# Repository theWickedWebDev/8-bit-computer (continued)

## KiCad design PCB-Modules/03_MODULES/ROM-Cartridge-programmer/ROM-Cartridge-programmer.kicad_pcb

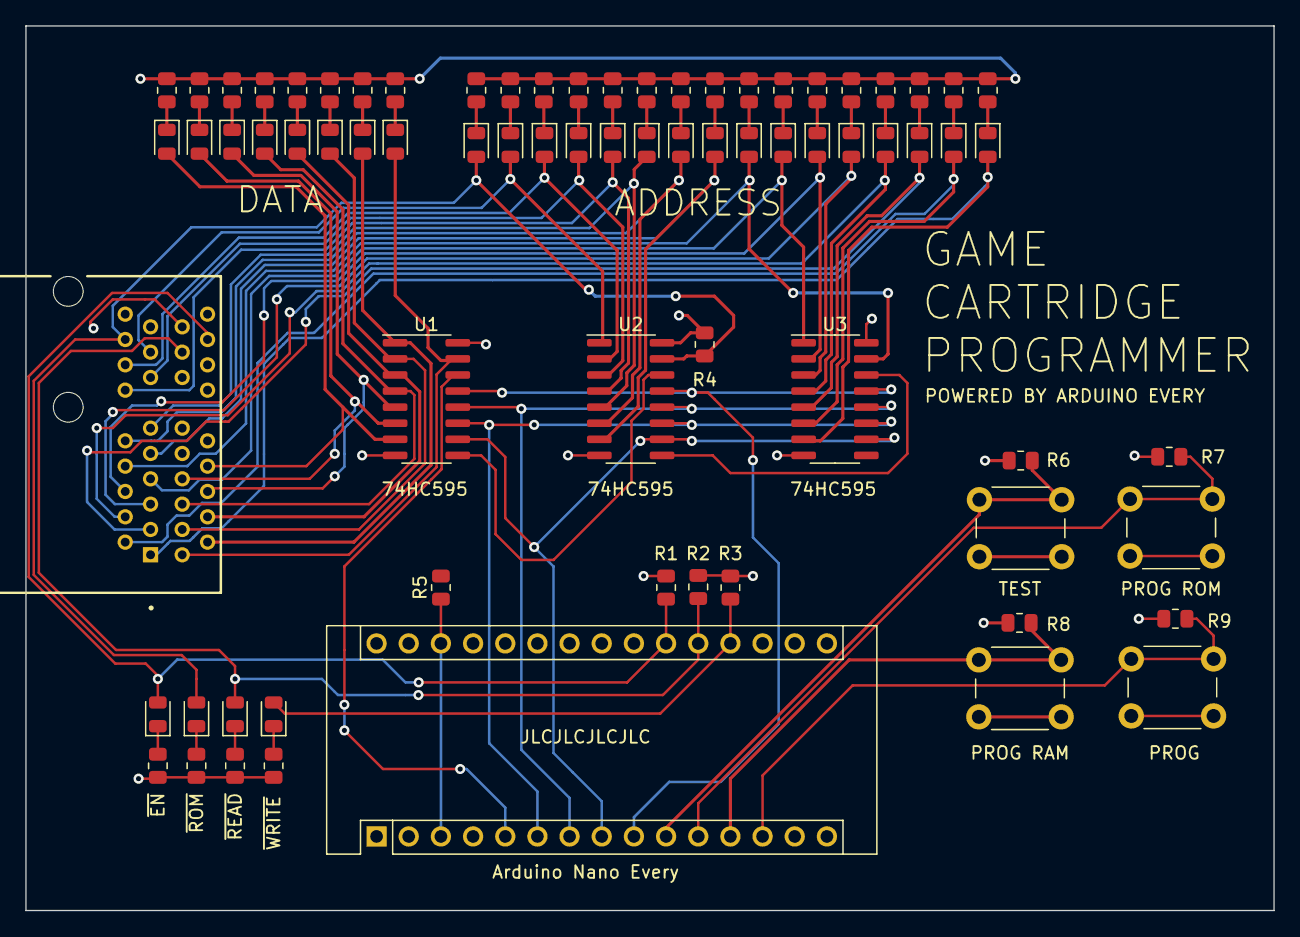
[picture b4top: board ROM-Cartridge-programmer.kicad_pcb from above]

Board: 4 copper layers, 98.6 x 69.8 mm, 74 parts (0 on the bottom side), 69 nets.

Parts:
A1: Arduino_Nano_Every; Arduino_Nano
D1, D2, D3, D4, D5, D6, D7, D8, D9, D10, D11, D12, D13, D14, D15, D16, D17, D18, D19, D20, D21, D22, D23, D24, D25, D26, D27, D28: LED; LED_0805_2012Metric
J1: PCIE-036-02-X-D-RA; SAMTEC_PCIE-036-02-X-D-RA
R1, R2, R3, R4, R5, R6, R7, R8, R9, R10, R11, R12, R13, R14, R15, R16, R17, R18, R19, R20, R21, R22, R23, R24, R25, R26, R27, R28, R29, R30, R31, R32, R33, R34, R35, R36, R37: R_Small_US; R_0805_2012Metric
SW1, SW2, SW3, SW4: SW_Push; SW_PUSH_6mm
U1, U2, U3: 74HC595; SOIC-16_3.9x9.9mm_P1.27mm

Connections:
/A0: D16.2 (A), J1.A01, U3.7 (QH)
/A1: D15.2 (A), J1.A02, U3.6 (QG)
/A2: D14.2 (A), J1.A03, U3.5 (QF)
/A3: D13.2 (A), J1.A04, U3.4 (QE)
/A4: D12.2 (A), J1.A05, U3.3 (QD)
/A5: D11.2 (A), J1.A06, U3.2 (QC)
/A6: D10.2 (A), J1.A07, U3.1 (QB)
/A7: D9.2 (A), J1.A08, U3.15 (QA)
/A8: D8.2 (A), J1.A09, U2.7 (QH)
/A9: D7.2 (A), J1.A10, U2.6 (QG)
/A10: D6.2 (A), J1.A11, U2.5 (QF)
/A11: D5.2 (A), J1.A12, U2.4 (QE)
/A12: D4.2 (A), J1.A13, U2.3 (QD)
/A13: D3.2 (A), J1.A14, U2.2 (QC)
/A14: D2.2 (A), J1.A15, U2.1 (QB)
/A15: D1.2 (A), D28.2 (A), J1.A16, R4.1, U2.15 (QA)
/CLOCK: A1.6 (D3), U1.11 (SRCLK), U2.11 (SRCLK), U3.11 (SRCLK)
/D0: D24.2 (A), J1.B01, U1.15 (QA)
/D1: D23.2 (A), J1.B02, U1.1 (QB)
/D2: D22.2 (A), J1.B03, U1.2 (QC)
/D3: D21.2 (A), J1.B04, U1.3 (QD)
/D4: D20.2 (A), J1.B05, U1.4 (QE)
/D5: D19.2 (A), J1.B06, U1.5 (QF)
/D6: D18.2 (A), J1.B07, U1.6 (QG)
/D7: D17.2 (A), J1.B08, U1.7 (QH)
/DATA: A1.5 (D2), U1.14 (SER)
/LATCH: A1.7 (D4), U1.12 (RCLK), U2.12 (RCLK), U3.12 (RCLK)
/PRAM: A1.12 (D9), R8.2, SW3.1
/PROG: A1.13 (D10), R9.2, SW4.1
/PROM: A1.11 (D8), R7.2, SW2.1
/TEST: A1.10 (D7), R6.2, SW1.1
/~EN: A1.21 (A2), D27.2 (A), J1.B16, R1.1
/~READ: A1.20 (A1), D26.2 (A), J1.B15, R2.1
/~RESET: A1.8 (D5), U1.10 (~SRCLR), U2.10 (~SRCLR), U3.10 (~SRCLR)
/~SR_OE: A1.9 (D6), U1.13 (~OE), U2.13 (~OE), U3.13 (~OE)
/~WRITE: A1.19 (A0), D25.2 (A), R3.1
GND: A1.4 (GND), A1.29 (GND), J1.B17, R1.2, R6.1, R7.1, R8.1, R9.1, R10.1, R11.1, R12.1, R13.1, R14.1, R15.1, R16.1, R17.1, R18.1, R19.1, R20.1, R21.1, R22.1, R23.1, R24.1, R25.1, R26.1, R27.1, R28.1, R29.1, R30.1, R31.1, R32.1, R33.1, R34.1, R35.1, R36.1, R37.1, U1.8 (GND), U2.8 (GND), U3.8 (GND)
unnamed: A1.3 (~RESET), A1.28 (~RESET), R5.1
unnamed: D1.1 (K), R10.2
unnamed: D2.1 (K), R11.2
unnamed: D3.1 (K), R12.2
unnamed: D4.1 (K), R13.2
unnamed: D5.1 (K), R14.2
unnamed: D6.1 (K), R15.2
unnamed: D7.1 (K), R16.2
unnamed: D8.1 (K), R17.2
unnamed: D9.1 (K), R18.2
unnamed: D10.1 (K), R19.2
unnamed: D11.1 (K), R20.2
unnamed: D12.1 (K), R21.2
unnamed: D13.1 (K), R22.2
unnamed: D14.1 (K), R23.2
unnamed: D15.1 (K), R24.2
unnamed: D16.1 (K), R25.2
unnamed: D17.1 (K), R26.2
unnamed: D18.1 (K), R27.2
unnamed: D19.1 (K), R28.2
unnamed: D20.1 (K), R29.2
unnamed: D21.1 (K), R30.2
unnamed: D22.1 (K), R31.2
unnamed: D23.1 (K), R32.2
unnamed: D24.1 (K), R33.2
unnamed: D25.1 (K), R34.2
unnamed: D26.1 (K), R35.2
unnamed: D27.1 (K), R36.2
unnamed: D28.1 (K), R37.2
unnamed: U2.9 (QH'), U3.14 (SER)
unnamed: U1.9 (QH'), U2.14 (SER)
VCC: A1.27 (+5V), J1.B18, R2.2, R3.2, R4.2, R5.2, SW1.2, SW2.2, SW3.2, SW4.2, U1.16 (VCC), U2.16 (VCC), U3.16 (VCC)

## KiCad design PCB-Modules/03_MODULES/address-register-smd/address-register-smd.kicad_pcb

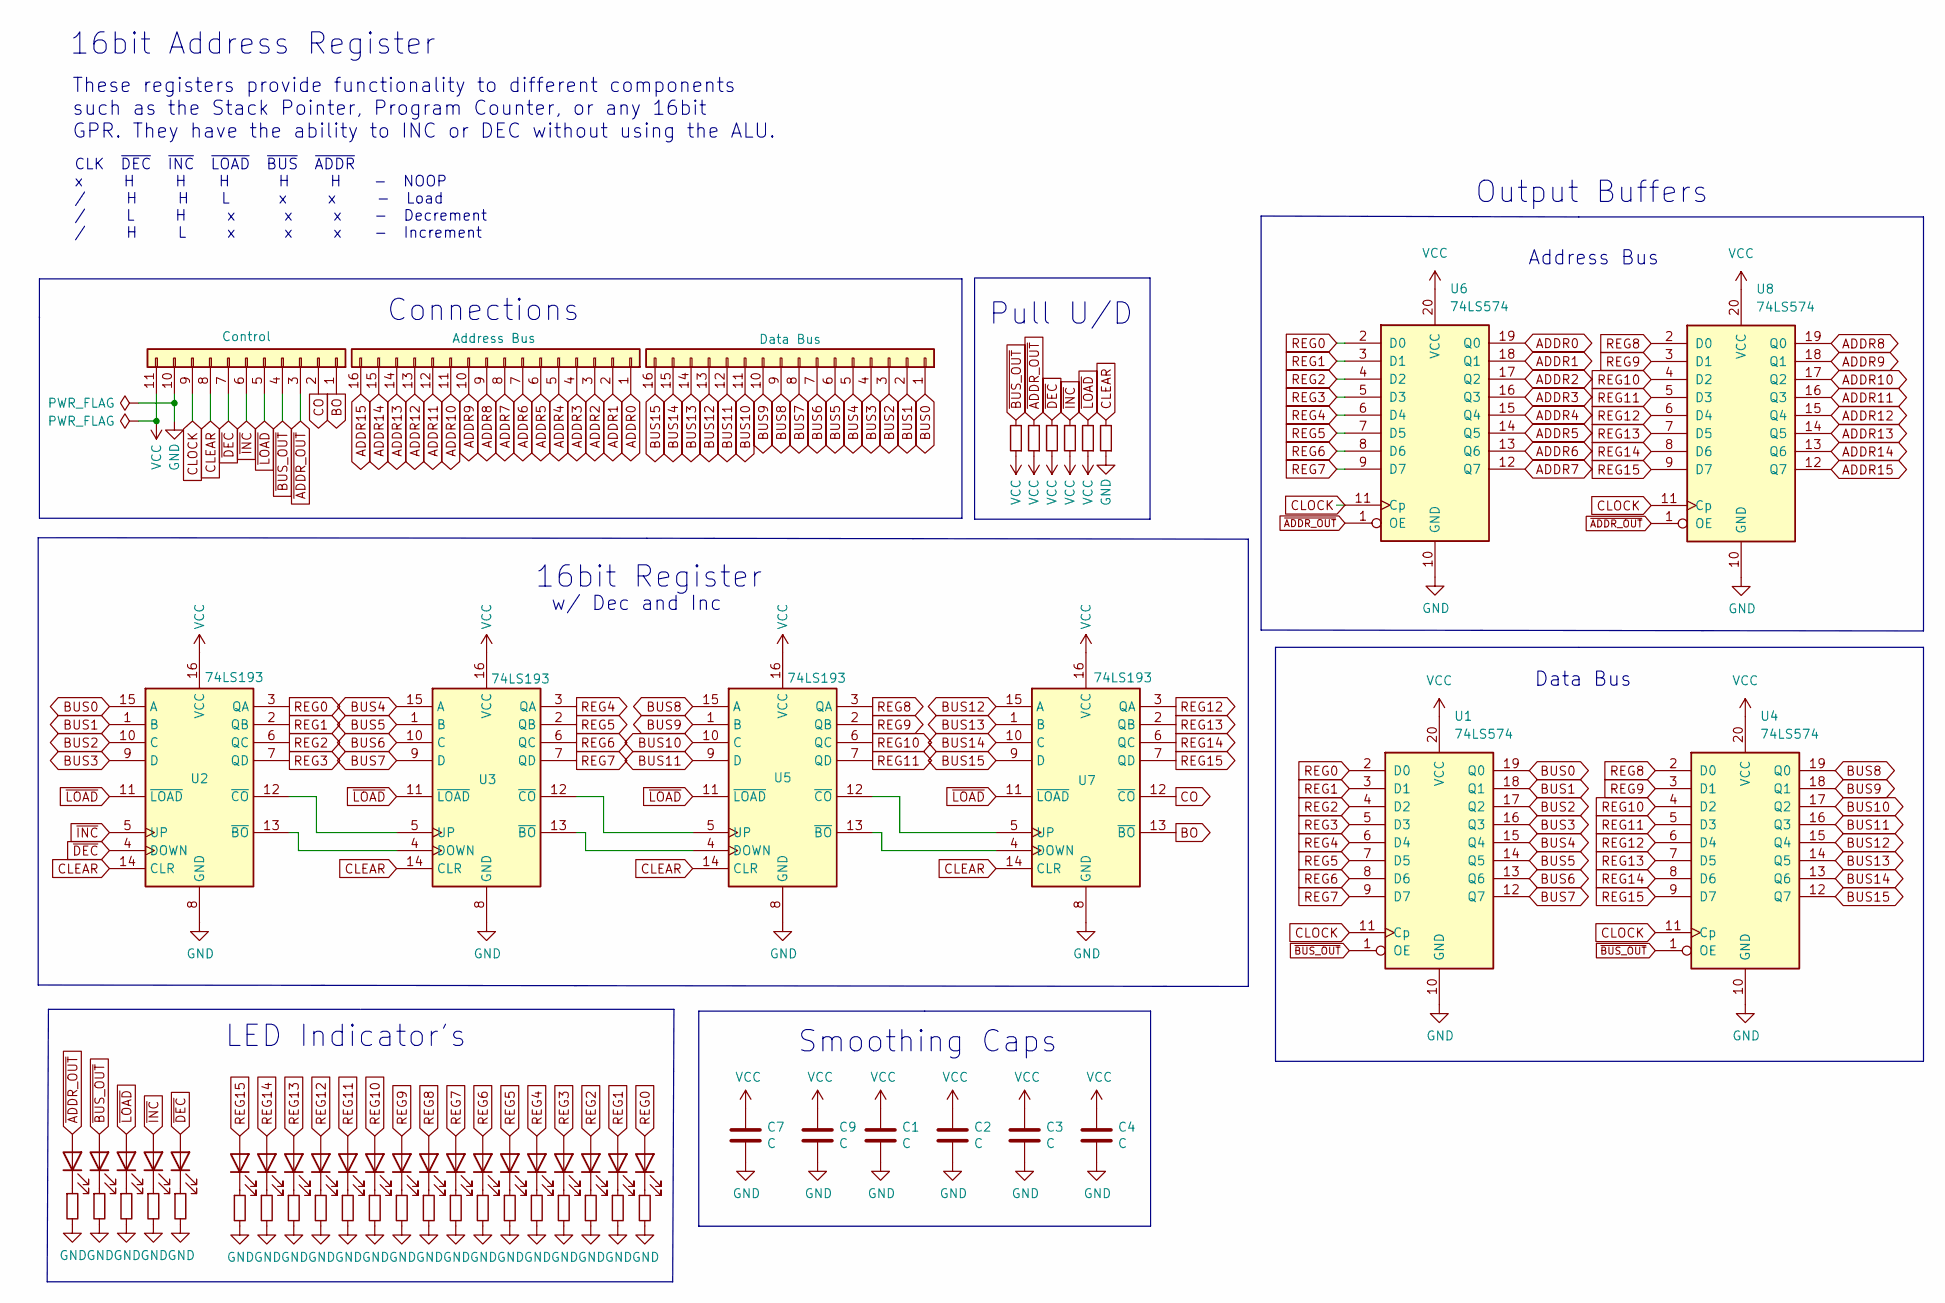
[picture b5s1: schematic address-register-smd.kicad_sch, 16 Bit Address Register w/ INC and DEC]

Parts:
C1, C2, C3, C4, C7, C9: C; C_0805_2012Metric
D1, D2, D3, D4, D5, D6, D7, D8, D9, D10, D11, D12, D13, D14, D15, D16, D18, D19, D20, D21, D22: LED; LED_1206_3216Metric
J2, J3: Conn_01x16; PinHeader_1x16_P2.54mm_Vertical
J4: Conn_01x11; PinHeader_1x11_P2.54mm_Vertical
R1, R2, R3, R4, R5, R6, R7, R8, R9, R10, R11, R12, R13, R14, R15, R16, R17, R18, R19, R20, R21, R22, R23, R24, R25, R27, R28: R_Small; R_0805_2012Metric
U1, U4, U6, U8: 74LS574; SO-20_5.3x12.6mm_P1.27mm
U2, U3, U5, U7: 74LS193; SO-16_5.3x10.2mm_P1.27mm

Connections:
ADDR0: J3.1, U6.19 (Q0)
ADDR1: J3.2, U6.18 (Q1)
ADDR2: J3.3, U6.17 (Q2)
ADDR3: J3.4, U6.16 (Q3)
ADDR4: J3.5, U6.15 (Q4)
ADDR5: J3.6, U6.14 (Q5)
ADDR6: J3.7, U6.13 (Q6)
ADDR7: J3.8, U6.12 (Q7)
ADDR8: J3.9, U8.19 (Q0)
ADDR9: J3.10, U8.18 (Q1)
ADDR10: J3.11, U8.17 (Q2)
ADDR11: J3.12, U8.16 (Q3)
ADDR12: J3.13, U8.15 (Q4)
ADDR13: J3.14, U8.14 (Q5)
ADDR14: J3.15, U8.13 (Q6)
ADDR15: J3.16, U8.12 (Q7)
BO: J4.1, U7.13 (~BO)
BUS0: J2.1, U1.19 (Q0), U2.15 (A)
BUS1: J2.2, U1.18 (Q1), U2.1 (B)
BUS2: J2.3, U1.17 (Q2), U2.10 (C)
BUS3: J2.4, U1.16 (Q3), U2.9 (D)
BUS4: J2.5, U1.15 (Q4), U3.15 (A)
BUS5: J2.6, U1.14 (Q5), U3.1 (B)
BUS6: J2.7, U1.13 (Q6), U3.10 (C)
BUS7: J2.8, U1.12 (Q7), U3.9 (D)
BUS8: J2.9, U4.19 (Q0), U5.15 (A)
BUS9: J2.10, U4.18 (Q1), U5.1 (B)
BUS10: J2.11, U4.17 (Q2), U5.10 (C)
BUS11: J2.12, U4.16 (Q3), U5.9 (D)
BUS12: J2.13, U4.15 (Q4), U7.15 (A)
BUS13: J2.14, U4.14 (Q5), U7.1 (B)
BUS14: J2.15, U4.13 (Q6), U7.10 (C)
BUS15: J2.16, U4.12 (Q7), U7.9 (D)
CLEAR: J4.8, R18.2, U2.14 (CLR), U3.14 (CLR), U5.14 (CLR), U7.14 (CLR)
CLOCK: J4.9, U1.11 (Cp), U4.11 (Cp), U6.11 (Cp), U8.11 (Cp)
CO: J4.2, U7.12 (~CO)
GND: C1.2, C2.2, C3.2, C4.2, C7.2, C9.2, J4.10, R2.2, R3.2, R4.2, R5.2, R6.2, R7.2, R8.2, R9.2, R10.2, R11.2, R12.2, R13.2, R14.2, R15.2, R16.2, R17.2, R18.1, R19.2, R20.2, R21.2, R22.2, R23.2, U1.10 (GND), U2.8 (GND), U3.8 (GND), U4.10 (GND), U5.8 (GND), U6.10 (GND), U7.8 (GND), U8.10 (GND)
unnamed: D1.1 (K), R2.1
unnamed: D2.1 (K), R3.1
unnamed: D3.1 (K), R4.1
unnamed: D4.1 (K), R5.1
unnamed: D5.1 (K), R6.1
unnamed: D6.1 (K), R7.1
unnamed: D7.1 (K), R8.1
unnamed: D8.1 (K), R9.1
unnamed: D9.1 (K), R10.1
unnamed: D10.1 (K), R11.1
unnamed: D11.1 (K), R12.1
unnamed: D12.1 (K), R13.1
unnamed: D13.1 (K), R14.1
unnamed: D14.1 (K), R15.1
unnamed: D15.1 (K), R16.1
unnamed: D16.1 (K), R19.1
unnamed: D18.1 (K), R20.1
unnamed: D19.1 (K), R21.1
unnamed: D20.1 (K), R22.1
unnamed: D21.1 (K), R23.1
unnamed: D22.1 (K), R17.1
unnamed: U2.12 (~CO), U3.5 (UP)
unnamed: U2.13 (~BO), U3.4 (DOWN)
unnamed: U3.12 (~CO), U5.5 (UP)
unnamed: U3.13 (~BO), U5.4 (DOWN)
unnamed: U5.12 (~CO), U7.5 (UP)
unnamed: U5.13 (~BO), U7.4 (DOWN)
REG0: D16.2 (A), U1.2 (D0), U2.3 (QA), U6.2 (D0)
REG1: D15.2 (A), U1.3 (D1), U2.2 (QB), U6.3 (D1)
REG2: D14.2 (A), U1.4 (D2), U2.6 (QC), U6.4 (D2)
REG3: D13.2 (A), U1.5 (D3), U2.7 (QD), U6.5 (D3)
REG4: D12.2 (A), U1.6 (D4), U3.3 (QA), U6.6 (D4)
REG5: D11.2 (A), U1.7 (D5), U3.2 (QB), U6.7 (D5)
REG6: D10.2 (A), U1.8 (D6), U3.6 (QC), U6.8 (D6)
REG7: D9.2 (A), U1.9 (D7), U3.7 (QD), U6.9 (D7)
REG8: D8.2 (A), U4.2 (D0), U5.3 (QA), U8.2 (D0)
REG9: D7.2 (A), U4.3 (D1), U5.2 (QB), U8.3 (D1)
REG10: D6.2 (A), U4.4 (D2), U5.6 (QC), U8.4 (D2)
REG11: D5.2 (A), U4.5 (D3), U5.7 (QD), U8.5 (D3)
REG12: D4.2 (A), U4.6 (D4), U7.3 (QA), U8.6 (D4)
REG13: D3.2 (A), U4.7 (D5), U7.2 (QB), U8.7 (D5)
REG14: D2.2 (A), U4.8 (D6), U7.6 (QC), U8.8 (D6)
REG15: D1.2 (A), U4.9 (D7), U7.7 (QD), U8.9 (D7)
VCC: C1.1, C2.1, C3.1, C4.1, C7.1, C9.1, J4.11, R1.1, R24.1, R25.1, R27.2, R28.2, U1.20 (VCC), U2.16 (VCC), U3.16 (VCC), U4.20 (VCC), U5.16 (VCC), U6.20 (VCC), U7.16 (VCC), U8.20 (VCC)
~ADDR_OUT: D20.2 (A), J4.3, R25.2, U6.1 (OE), U8.1 (OE)
~BUS_OUT: D18.2 (A), J4.4, R1.2, U1.1 (OE), U4.1 (OE)
~DEC: D19.2 (A), J4.7, R27.1, U2.4 (DOWN)
~INC: D21.2 (A), J4.6, R28.1, U2.5 (UP)
~LOAD: D22.2 (A), J4.5, R24.2, U2.11 (~LOAD), U3.11 (~LOAD), U5.11 (~LOAD), U7.11 (~LOAD)

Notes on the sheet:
Data Bus
16bit Register
w/ Dec and Inc
Smoothing Caps
Output Buffers
LED Indicator's
Address Bus
Pull U/D
Connections
CLK ~{DEC} ~{INC} ~{LOAD} ~{BUS} ~{ADDR} x H H H H H - NOOP / H H L x x - Load / L H x x x - Decrement / H L x x x - Increment
These registers provide functionality to different components such as the Stack Pointer, Program Counter, or any 16bit GPR. They have the ability to INC or DEC without using the ALU.
16bit Address Register

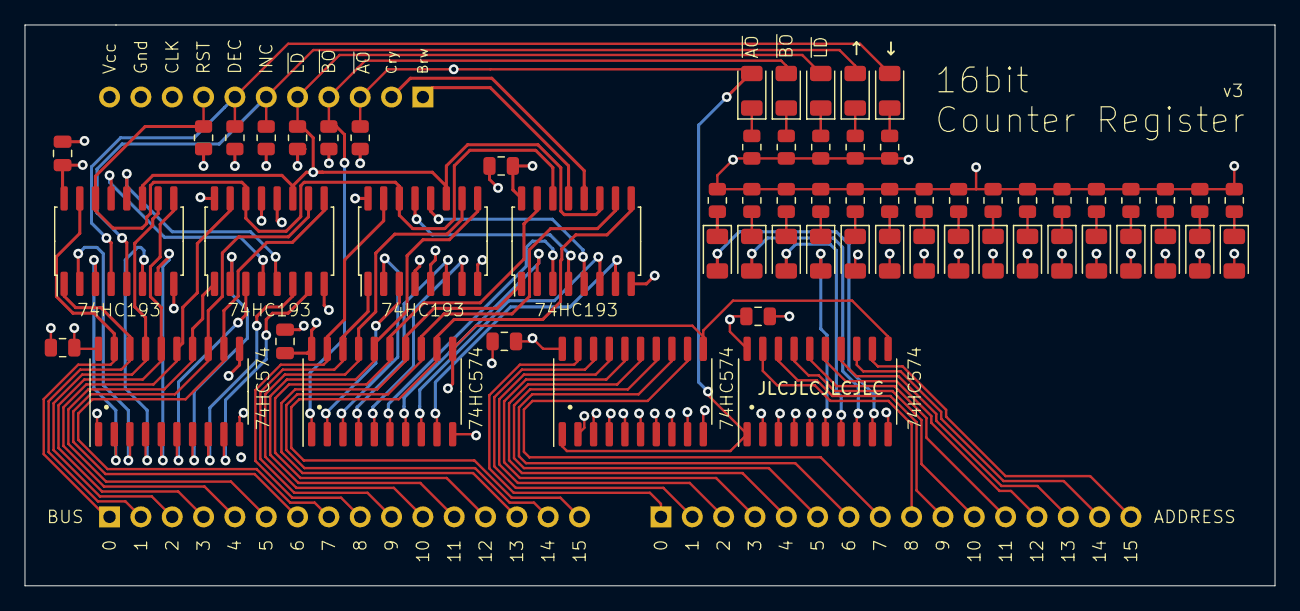
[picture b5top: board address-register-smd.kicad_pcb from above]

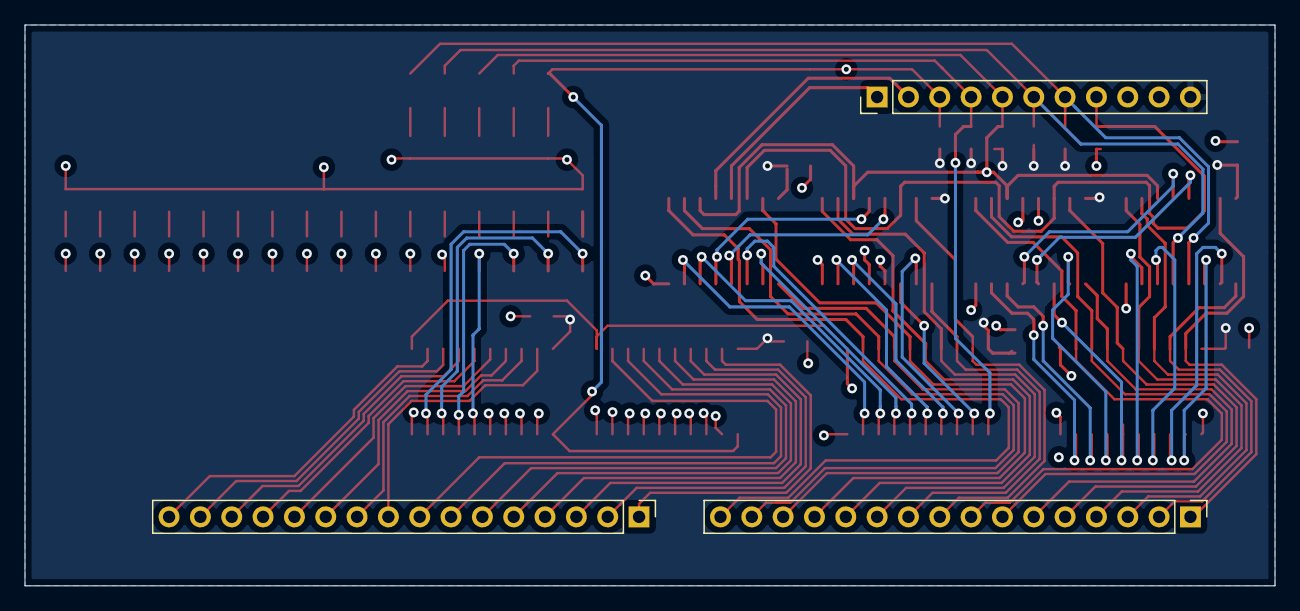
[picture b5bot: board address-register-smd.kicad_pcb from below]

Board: 4 copper layers, 101.3 x 45.5 mm, 65 parts (3 on the bottom side), 86 nets.

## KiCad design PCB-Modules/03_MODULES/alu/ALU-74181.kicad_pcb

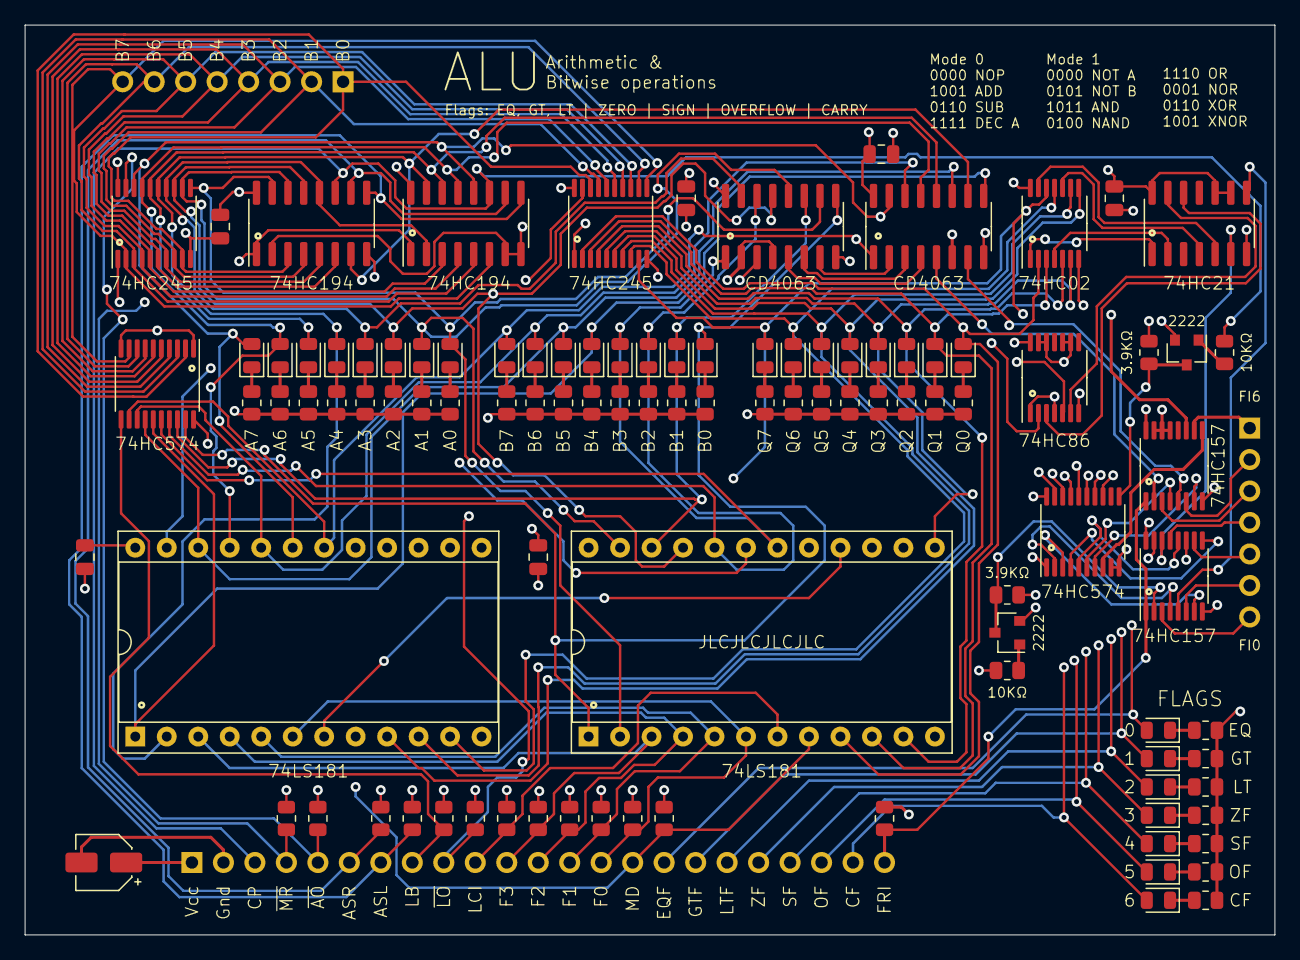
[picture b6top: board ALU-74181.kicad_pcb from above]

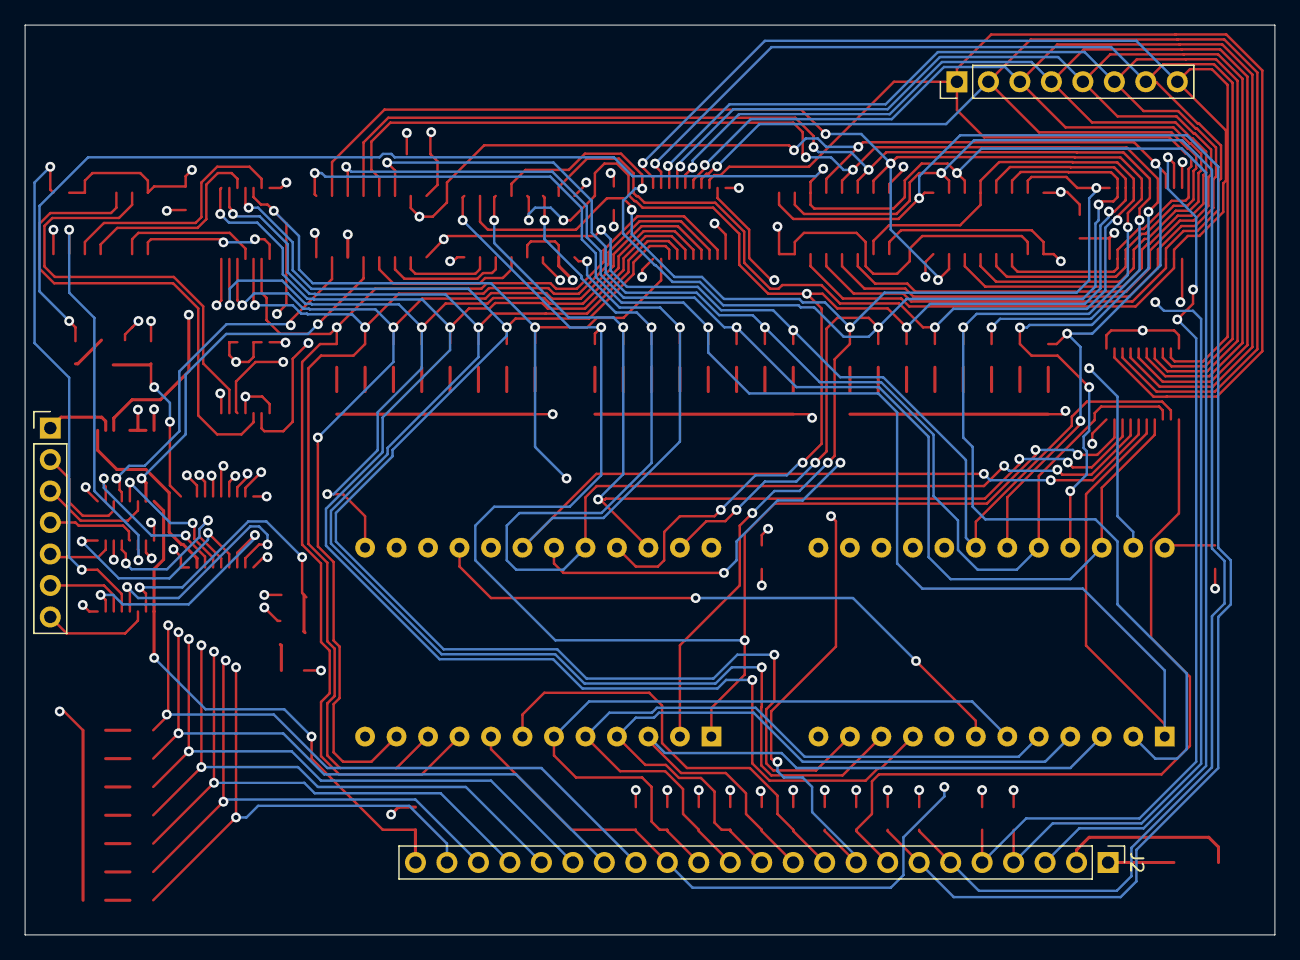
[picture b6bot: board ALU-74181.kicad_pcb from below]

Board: 4 copper layers, 100.8 x 73.4 mm, 106 parts (3 on the bottom side), 120 nets.

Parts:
C1, C2, C3, C4, C5, C7: C; C_0805_2012Metric
C6: CP; CP_Elec_4x3.9
D1, D2, D3, D4, D5, D6, D7, D8, D9, D10, D11, D12, D13, D14, D15, D16, D17, D18, D19, D20, D21, D22, D23, D24, D25, D26, D27, D28, D29, D30, D31: LED; LED_0805_2012Metric
J1: Conn_01x08; PinHeader_1x08_P2.54mm_Vertical
J2: Conn_01x23; PinHeader_1x23_P2.54mm_Vertical
J3: Conn_01x07; PinHeader_1x07_P2.54mm_Vertical
Q1, Q2: PMBT2222; SOT-23
R1, R4, R5, R6, R7, R8, R9, R10, R11, R12, R13, R14, R15, R16, R17, R18, R19, R20, R21, R22, R23, R24, R25, R26, R27, R28, R29, R30, R31, R32, R33, R34, R35, R36, R38, R39, R40, R41, R42, R43, R44, R45, R46, R47: R_US; R_0805_2012Metric
R2, R3: 10kohm; R_0805_2012Metric
R37, R48: 3.9kohm; R_0805_2012Metric
U1, U2: 74HC245; TSSOP-20_4.4x6.5mm_P0.65mm
U3, U12: 74LS574; TSSOP-20_4.4x6.5mm_P0.65mm
U4, U7: 74LS194; SOIC-16_3.9x9.9mm_P1.27mm
U5: 74HC86PW,118; TSSOP-14_4.4x5mm_P0.65mm
U6, U8: 74LS181; DIP-24_W15.24mm_Socket
U9: 74LS02; TSSOP-14_4.4x5mm_P0.65mm
U10, U13: CD4063; SOIC-16_3.9x9.9mm_P1.27mm
U11: 74LS21; SOIC-14_3.9x8.7mm_P1.27mm
U14, U15: 74LS157; TSSOP-16_4.4x5mm_P0.65mm

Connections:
/A0: D15.2, U2.11, U4.15, U8.2, U10.10
/A1: D14.2, U2.12, U4.14, U8.23, U10.12
/A2: D13.2, U2.13, U4.13, U8.21, U10.13
/A3: D12.2, U2.14, U4.12, U7.2, U8.19, U10.15
/A4: D11.2, U2.15, U4.7, U6.2, U7.15, U13.10
/A5: D10.2, U2.16, U6.23, U7.14, U13.12
/A6: D9.2, U2.17, U6.21, U7.13, U13.13
/A7: D8.2, U2.18, U5.2, U6.19, U7.12, U13.15
/ALU0: D31.2, U1.2, U8.9, U9.2
/ALU1: D30.2, U1.3, U8.10, U9.3
/ALU2: D29.2, U1.4, U8.11, U9.5
/ALU3: D28.2, U1.5, U8.13, U9.6
/ALU4: D27.2, U1.6, U6.9, U9.8
/ALU5: D26.2, U1.7, U6.10, U9.9
/ALU6: D25.2, U1.8, U6.11, U9.11
/ALU7: D24.2, U1.9, U5.1, U5.4, U6.13, U9.12, U14.11
/B0: D23.2, U3.19, U8.1, U10.9
/B1: D22.2, U3.18, U8.22, U10.11
/B2: D21.2, U3.17, U8.20, U10.14
/B3: D20.2, U3.16, U8.18, U10.1
/B4: D19.2, U3.15, U6.1, U13.9
/B5: D18.2, U3.14, U6.22, U13.11
/B6: D17.2, U3.13, U6.20, U13.14
/B7: D16.2, U3.12, U5.5, U6.18, U13.1
ALU_CARRY_IN: J2.10, R35.1, U8.7
ALU_CARRY_OUT: R3.1, U6.16
ALU_F0: J2.14, R42.1, U6.6, U8.6
ALU_F1: J2.13, R43.1, U6.5, U8.5
ALU_F2: J2.12, R44.1, U6.4, U8.4
ALU_F3: J2.11, R45.1, U6.3, U8.3
ALU_MODE: J2.15, R41.1, U6.8, U8.8
A_SHL: J2.7, R38.1, U4.9, U7.9
A_SHR: J2.6, R39.1, U4.10, U7.10
BUS0: J1.1, U1.18, U2.9, U3.2, U4.3
BUS1: J1.2, U1.17, U2.8, U3.3, U4.4
BUS2: J1.3, U1.16, U2.7, U3.4, U4.5
BUS3: J1.4, U1.15, U2.6, U3.5, U4.6
BUS4: J1.5, U1.14, U2.5, U3.6, U7.3
BUS5: J1.6, U1.13, U2.4, U3.7, U7.4
BUS6: J1.7, U1.12, U2.3, U3.8, U7.5
BUS7: J1.8, U1.11, U2.2, U3.9, U7.6
CF: D1.2, J2.22, U12.19
CLOCK: J2.3, R2.1, U4.11, U7.11
EQ: U13.6, U15.11
EQF: D7.2, J2.16, U12.13
FLAG0: U12.2, U14.4
FLAG1: U12.3, U14.7
FLAG2: U12.4, U14.9
FLAG3: U12.5, U14.12
FLAG4: U12.6, U15.4
FLAG5: U12.7, U15.7
FLAG6: U12.8, U15.9
FLAG_IN_0: J3.7, U14.3
FLAG_IN_1: J3.6, U14.6
FLAG_IN_2: J3.5, U14.10
FLAG_IN_3: J3.4, U14.13
FLAG_IN_4: J3.3, U15.3
FLAG_IN_5: J3.2, U15.6
FLAG_IN_6: J3.1, U15.10
FLAG_REG_IN: J2.23, R47.1, U14.1, U15.1
GND: C1.2, C2.2, C3.2, C4.2, C5.2, C6.2, C7.2, J2.2, Q1.2, Q2.2, R4.2, R5.2, R6.2, R7.2, R8.2, R9.2, R10.2, R11.2, R12.2, R13.2, R14.2, R15.2, R16.2, R17.2, R18.2, R19.2, R20.2, R21.2, R22.2, R23.2, R24.2, R25.2, R26.2, R27.2, R28.2, R29.2, R30.2, R31.2, R32.2, R33.2, R34.2, R38.2, R39.2, R41.2, R42.2, R43.2, R44.2, R45.2, R47.2, U1.10, U2.1, U2.10, U3.1, U3.10, U4.2, U4.8, U5.7, U5.9, U5.10, U5.12, U5.13, U6.12, U7.7, U7.8, U8.12, U9.7, U10.2, U10.4, U10.8, U11.7, U12.1, U12.9, U12.10, U13.8, U14.8, U14.15, U15.8, U15.13, U15.14, U15.15
GT: U13.7, U15.5
GTF: D6.2, J2.17, U12.14
LOAD_B: J2.8, R1.1, U3.11
LT: U13.5, U15.2
LTF: D5.2, J2.18, U12.15
unnamed: D1.1, R4.1
unnamed: D2.1, R5.1
unnamed: D3.1, R6.1
unnamed: D4.1, R7.1
unnamed: D5.1, R8.1
unnamed: D6.1, R9.1
unnamed: D7.1, R10.1
unnamed: D8.1, R11.1
unnamed: D9.1, R12.1
unnamed: D10.1, R13.1
unnamed: D11.1, R14.1
unnamed: D12.1, R15.1
unnamed: D13.1, R16.1
unnamed: D14.1, R17.1
unnamed: D15.1, R18.1
unnamed: D16.1, R19.1
unnamed: D17.1, R20.1
unnamed: D18.1, R21.1
unnamed: D19.1, R22.1
unnamed: D20.1, R23.1
unnamed: D21.1, R24.1
unnamed: D22.1, R25.1
unnamed: D23.1, R26.1
unnamed: D24.1, R27.1
unnamed: D25.1, R28.1
unnamed: D26.1, R29.1
unnamed: D27.1, R30.1
unnamed: D28.1, R31.1
unnamed: D29.1, R32.1
unnamed: D30.1, R33.1
unnamed: D31.1, R34.1
unnamed: Q1.1, R2.2
unnamed: Q1.3, R37.1, U12.11
unnamed: Q2.1, R3.2
unnamed: Q2.3, R48.1, U14.2
unnamed: U6.7, U8.16
unnamed: U10.5, U13.4
unnamed: U10.6, U13.3
unnamed: U10.7, U13.2
unnamed: U9.1, U11.1
unnamed: U9.4, U11.2
unnamed: U9.10, U11.4
unnamed: U9.13, U11.5
unnamed: U5.3, U11.12
unnamed: U5.6, U11.13
OF: D2.2, J2.21, U12.18
OVERFLOW: U11.8, U14.5
SF: D3.2, J2.20, U12.17
VCC: C1.1, C2.1, C3.1, C4.1, C5.1, C6.1, C7.1, J2.1, R1.2, R35.2, R36.2, R37.2, R40.2, R46.2, R48.2, U1.1, U1.20, U2.20, U3.20, U4.16, U5.14, U6.24, U7.16, U8.24, U9.14, U10.3, U10.16, U11.9, U11.10, U11.14, U12.20, U13.16, U14.16, U15.16
ZERO: U11.6, U14.14
ZF: D4.2, J2.19, U12.16
~ALU_OUT: J2.9, R36.1, U1.19
~A_OUT: J2.5, R40.1, U2.19
~RESET: J2.4, R46.1, U4.1, U7.1

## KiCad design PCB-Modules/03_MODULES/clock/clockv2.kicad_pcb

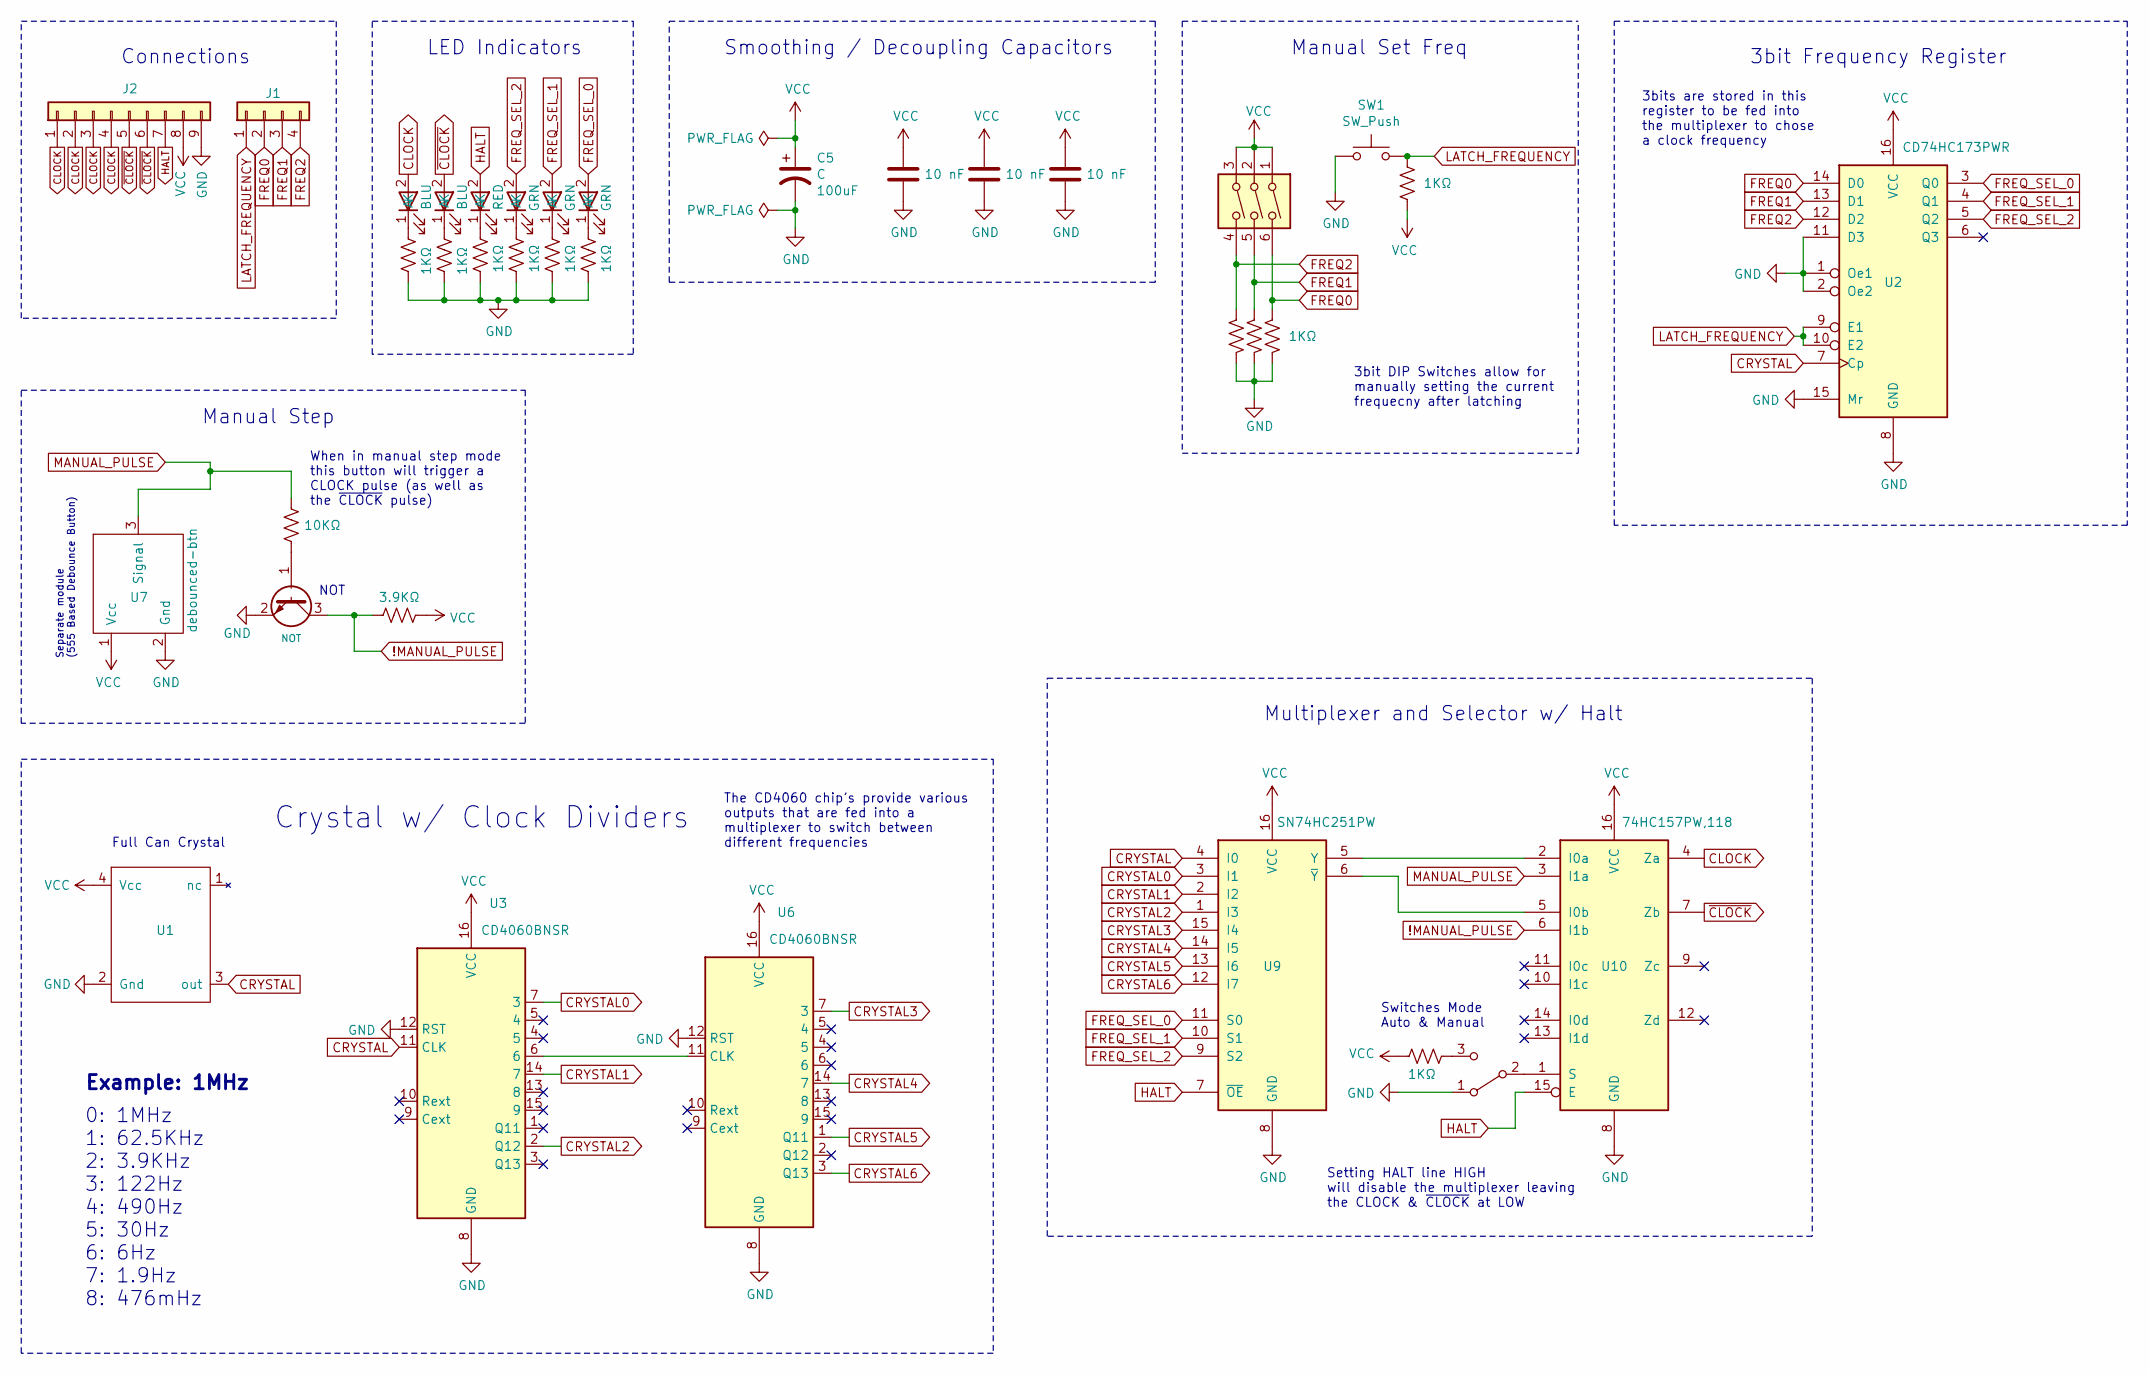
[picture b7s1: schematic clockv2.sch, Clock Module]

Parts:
C1, C2, C3: 885382207009; C_0805_2012Metric
C5: C; CP_Elec_8x10
J1: Conn_01x04; PinHeader_1x04_P2.54mm_Vertical
J2: Conn_01x09; PinHeader_1x09_P2.54mm_Vertical
Q1: PMBT2222; SOT-23
R1, R2, R3, R4, R5, R6, R7, R8, R11, R12, R13: 1kohm; R_0805_2012Metric
R9: 10kohm; R_0805_2012Metric
R10: 3.9kohm; R_0805_2012Metric
SW1: SW_Push; SW_PUSH_6mm
SW2: SW_DPDT_x2; THT-DPDT
SW3: SW_DIP_x03; SW_DIP_SPSTx03_Slide_9.78x9.8mm_W7.62mm_P2.54mm
U1: full-can-crystal; full-can-14pin
U2: CD74HC173PWR; TSSOP-16_4.4x5mm_P0.65mm
U3, U6: CD4060BNSR; SOIC-16_4.55x10.3mm_P1.27mm
U4, U5, U8: 19-217_GHC-YR1S2_3T; LED_1206_3216Metric
U7: debounced-btn; breakout-debounce-btn
U9: SN74HC251PW; TSSOP-16_4.4x5mm_P0.65mm
U10: 74HC157PW,118; TSSOP-16_4.4x5mm_P0.65mm
U11: NCD0805R1; LED_1206_3216Metric
U12, U13: 19-217_BHC-ZL1M2RY_3T; LED_1206_3216Metric

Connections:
!MANUAL_PULSE: Q1.3 (E), R10.2, U10.6 (I1b)
CLOCK: J2.1, J2.2, J2.3, J2.4, U10.4 (Za), U12.2 (A)
CRYSTAL: U1.3 (out), U2.7 (Cp), U3.11 (CLK), U9.4 (I0)
CRYSTAL0: U3.7 (3), U9.3 (I1)
CRYSTAL1: U3.14 (7), U9.2 (I2)
CRYSTAL2: U3.2 (Q12), U9.1 (I3)
CRYSTAL3: U6.7 (3), U9.15 (I4)
CRYSTAL4: U6.14 (7), U9.14 (I5)
CRYSTAL5: U6.1 (Q11), U9.13 (I6)
CRYSTAL6: U6.3 (Q13), U9.12 (I7)
FREQ0: J1.2, R11.1, SW3.6, U2.14 (D0)
FREQ1: J1.3, R12.1, SW3.5, U2.13 (D1)
FREQ2: J1.4, R13.1, SW3.4, U2.12 (D2)
FREQ_SEL_0: U2.3 (Q0), U5.2 (A), U9.11 (S0)
FREQ_SEL_1: U2.4 (Q1), U4.2 (A), U9.10 (S1)
FREQ_SEL_2: U2.5 (Q2), U8.2 (A), U9.9 (S2)
GND: C1.2, C2.2, C3.2, C5.2, J2.9, Q1.2 (C), R2.2, R3.2, R4.2, R5.2, R7.1, R8.1, R11.2, R12.2, R13.2, SW1.1, SW2.1 (A), U1.2 (Gnd), U2.1 (Oe1), U2.2 (Oe2), U2.8 (GND), U2.11 (D3), U2.15 (Mr), U3.8 (GND), U3.12 (RST), U6.8 (GND), U6.12 (RST), U7.2 (Gnd), U9.8 (GND), U10.8 (GND)
HALT: J2.7, U9.7 (~OE), U10.15 (E), U11.2 (A)
LATCH_FREQUENCY: J1.1, R1.2, SW1.2, U2.9 (E1), U2.10 (E2)
MANUAL_PULSE: R9.1, U7.3 (Signal), U10.3 (I1a)
unnamed: Q1.1 (B), R9.2
unnamed: R2.1, U8.1 (K)
unnamed: R3.1, U4.1 (K)
unnamed: R4.1, U5.1 (K)
unnamed: R5.1, U11.1 (K)
unnamed: R6.1, SW2.3 (C)
unnamed: R7.2, U12.1 (K)
unnamed: R8.2, U13.1 (K)
unnamed: SW2.2 (B), U10.1 (S)
unnamed: U3.6, U6.11 (CLK)
unnamed: U9.5 (Y), U10.2 (I0a)
unnamed: U9.6 (~Y), U10.5 (I0b)
VCC: C1.1, C2.1, C3.1, C5.1, J2.8, R1.1, R6.2, R10.1, SW3.1, SW3.2, SW3.3, U1.4 (Vcc), U2.16 (VCC), U3.16 (VCC), U6.16 (VCC), U7.1 (Vcc), U9.16 (VCC), U10.16 (VCC)
~CLOCK: J2.5, J2.6, U10.7 (Zb), U13.2 (A)

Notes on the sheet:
Smoothing / Decoupling Capacitors
Connections
LED Indicators
Manual Step
Manual Set Freq
3bit Frequency Register
Crystal w/ Clock Dividers
Full Can Crystal
Multiplexer and Selector w/ Halt
0: 1MHz 1: 62.5KHz 2: 3.9KHz 3: 122Hz 4: 490Hz 5: 30Hz 6: 6Hz 7: 1.9Hz 8: 476mHz
Example: 1MHz
The CD4060 chip’s provide various outputs that are fed into a multiplexer to switch between different frequencies
Separate module (555 Based Debounce Button)
NOT
3bit DIP Switches allow for manually setting the current frequecny after latching
3bits are stored in this register to be fed into the multiplexer to chose a clock frequency
Switches Mode Auto & Manual
Setting HALT line HIGH will disable the multiplexer leaving the CLOCK & ~CLOCK~ at LOW
When in manual step mode this button will trigger a CLOCK pulse (as well as the ~CLOCK~ pulse)

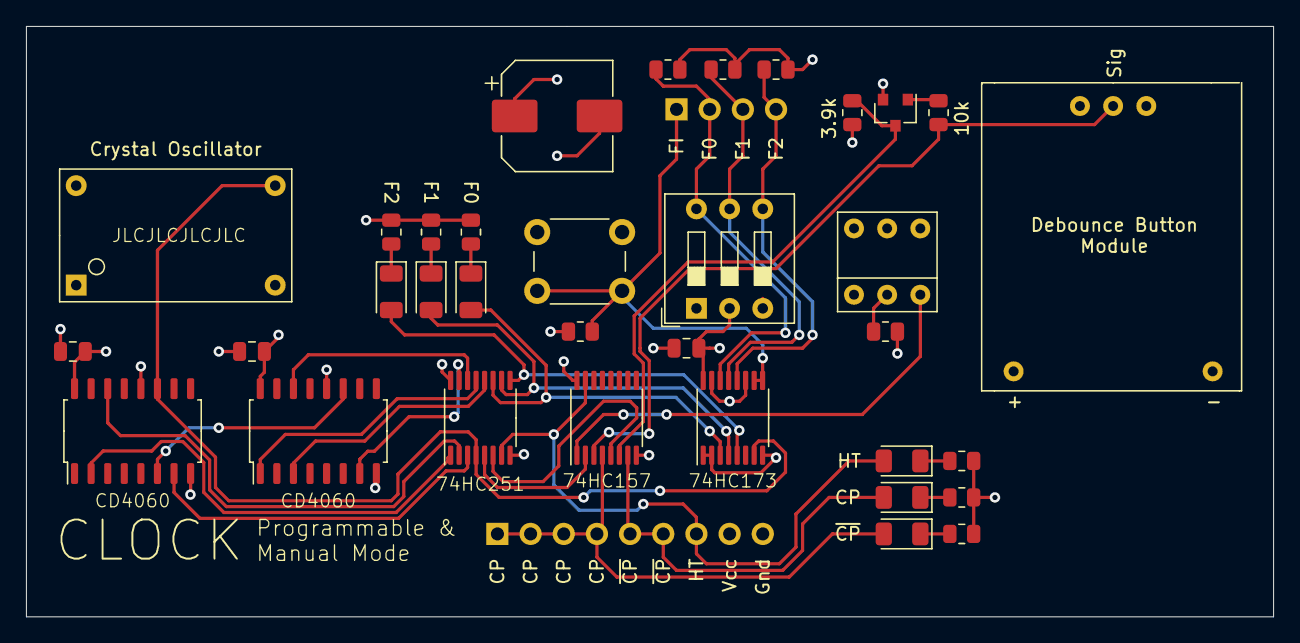
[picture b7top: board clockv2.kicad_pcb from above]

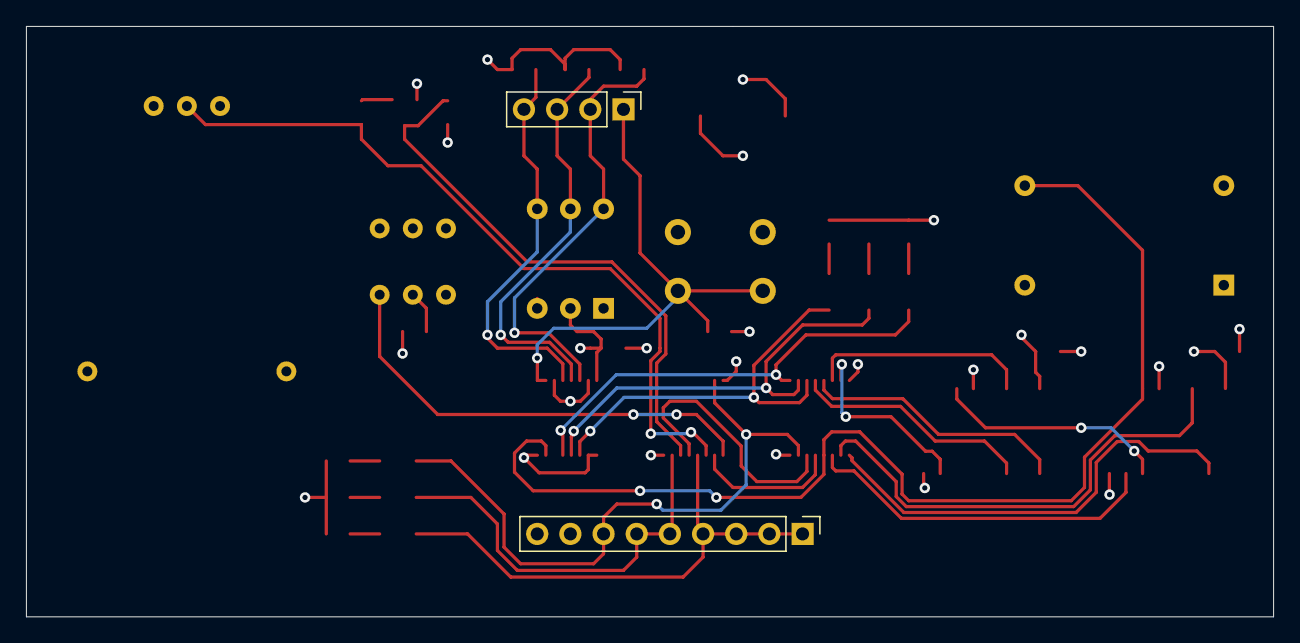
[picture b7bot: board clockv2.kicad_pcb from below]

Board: 4 copper layers, 95.5 x 45.2 mm, 36 parts (2 on the bottom side), 34 nets.
